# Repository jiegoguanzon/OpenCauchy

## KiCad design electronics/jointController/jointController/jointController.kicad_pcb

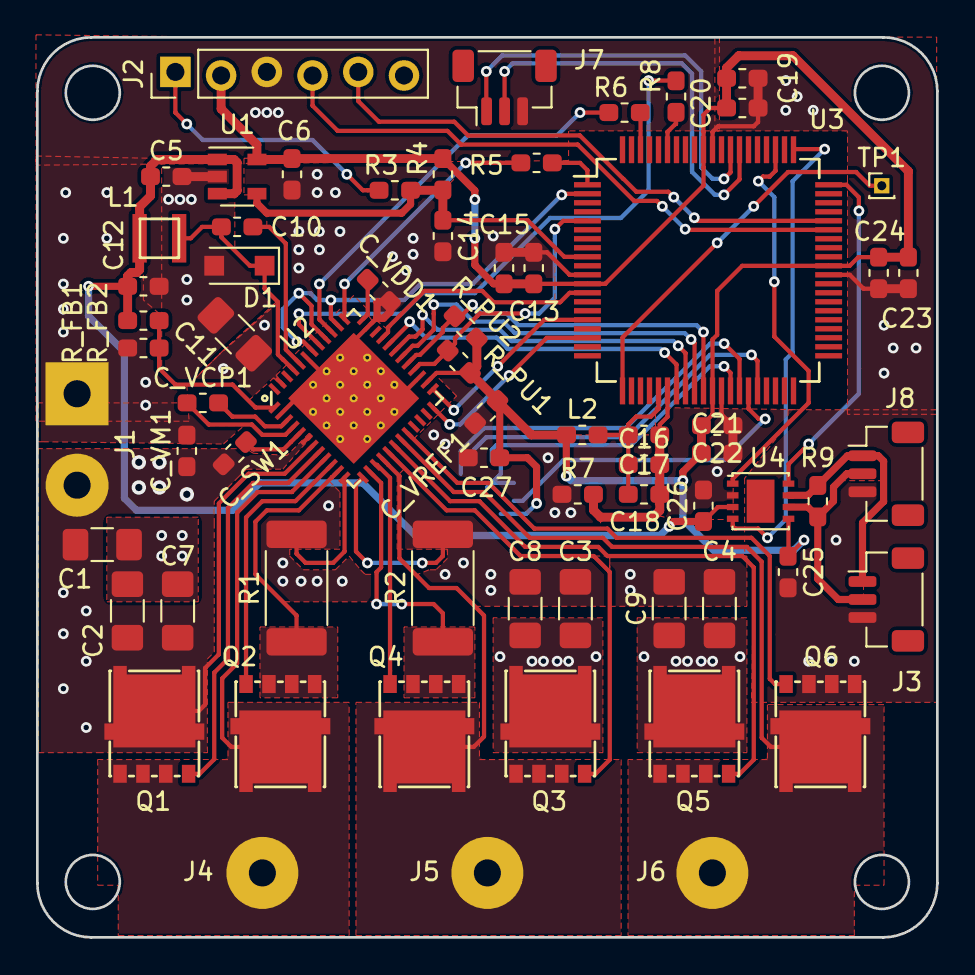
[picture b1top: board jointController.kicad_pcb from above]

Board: 2 copper layers, 50.0 x 50.0 mm, 68 parts (1 on the bottom side), 55 nets.

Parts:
C1, C2, C3, C4, C7, C8, C9, C11: 10uF; C_1206_3216Metric_Pad1.42x1.75mm_HandSolder
C5, C6, C16: 10uF; C_0603_1608Metric_Pad1.05x0.95mm_HandSolder
C10, C15, C17, C18, C20, C21, C23, C25, C26: 0.1uF; C_0603_1608Metric_Pad1.05x0.95mm_HandSolder
C12: 22uF; C_0603_1608Metric_Pad1.05x0.95mm_HandSolder
C13, C19, C22, C24: 0.01uF; C_0603_1608Metric_Pad1.05x0.95mm_HandSolder
C14: 470pF; C_0603_1608Metric_Pad1.05x0.95mm_HandSolder
C27: 1uF; C_0603_1608Metric_Pad1.05x0.95mm_HandSolder
C_SW1: 1uF; C_0603_1608Metric_Pad1.05x0.95mm_HandSolder
C_VCP1: 47nF; C_0603_1608Metric_Pad1.05x0.95mm_HandSolder
C_VDD1: 1uF; C_0603_1608Metric_Pad1.05x0.95mm_HandSolder
C_VM1: 0.1uF; C_0603_1608Metric_Pad1.05x0.95mm_HandSolder
C_VREF1: 0.1uF; C_0603_1608Metric_Pad1.05x0.95mm_HandSolder
D1: D_Schottky; D_SOD-123F
J1: PWR_IN; SolderWirePad_1x02_P5.08mm_Drill1.5mm
J2: ICSP; PinHeader_1x06_P2.54mm_Vertical_Staggered
J3, J8: CAN; JST_SH_BM03B-SRSS-TB_1x03-1MP_P1.00mm_Vertical
J4: A_OUT; SolderWirePad_1x01_Drill1.5mm
J5: B_OUT; SolderWirePad_1x01_Drill1.5mm
J6: C_OUT; SolderWirePad_1x01_Drill1.5mm
J7: UART1; JST_SH_BM03B-SRSS-TB_1x03-1MP_P1.00mm_Vertical
L1: 22uH; NRH3012T220MN
L2: 600R; L_0603_1608Metric_Pad1.05x0.95mm_HandSolder
Q1, Q2, Q3, Q4, Q5, Q6: NTMFS4935NT1G; 8-SOFL
R1, R2: 1m; R_2512_6332Metric_Pad1.52x3.35mm_HandSolder
R3, R7: 0; R_0603_1608Metric_Pad1.05x0.95mm_HandSolder
R4: 10k; R_0603_1608Metric_Pad1.05x0.95mm_HandSolder
R5, R6, R8: 75; R_0603_1608Metric_Pad1.05x0.95mm_HandSolder
R9: 120; R_0603_1608Metric_Pad1.05x0.95mm_HandSolder
R_FB1: 54.9k; R_0603_1608Metric_Pad1.05x0.95mm_HandSolder
R_FB2: 10k; R_0603_1608Metric_Pad1.05x0.95mm_HandSolder
R_PU1, R_PU2: 10k; R_0603_1608Metric_Pad1.05x0.95mm_HandSolder
TP1: DACOUT1; PinHeader_1x01_P1.00mm_Vertical
U1: MCP1755-3v3; SOT-23-5
U2: DRV8323RS; VQFN-48-7x7-P0.5
U3: dsPIC33CK256MP508; TQFP-80_12x12mm_P0.5mm
U4: MCP2562-E-MF; DFN-8-1EP_3x3mm_P0.65mm_EP1.55x2.4mm
U5: MA702; QFN-16-1EP_3x3mm_P0.5mm_EP1.8x1.8mm

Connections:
+3V3: C6.1, C13.2, C15.2, C19.2, C20.2, C21.2, C22.2, C23.1, C24.1, C25.1, C27.1, C_VREF1.1, J2.2, L2.1, R4.1, R_PU1.1, R_PU2.1, U1.5, U2.26, U3.12, U3.31, U3.51, U3.71, U4.5, U5.13
+5V: C5.1, C12.1, C26.1, L1.2, R_FB1.1, U1.1, U1.3, U4.3
A_OUT: J4.1, Q1.3, Q2.1, U2.9
B_OUT: J5.1, Q3.3, Q4.1, U2.16
CANH: J3.1, J8.1, R9.1, U4.7
CANL: J3.2, J8.2, R9.2, U4.6
CAN_RX: U3.61, U4.4
CAN_TX: U3.63, U4.1
C_OUT: J6.1, Q5.3, Q6.1, U2.19
DRV_ENABLE: U2.33, U3.13
DRV_MISO: R_PU2.2, U2.29, U3.30
DRV_MOSI: U2.30, U3.29
DRV_SCLK: U2.31, U3.28
DRV_nSCS: U2.32, U3.27
ENC_MISO: U3.33, U5.7
ENC_MOSI: U3.34, U5.4
ENC_SCLK: U3.35, U5.12
ENC_nSCS: U3.36, U5.5
GHA: Q1.2, U2.8
GHB: Q3.2, U2.17
GHC: Q5.2, U2.18
GLA: Q2.2, U2.10
GLB: Q4.2, U2.15
GLC: Q6.2, U2.20
GNDA: C16.2, C17.1, C18.2, R7.2, U3.26
unnamed: C10.1, U2.44
unnamed: C10.2, D1.1, L1.1, U2.45
unnamed: C16.1, C17.2, C18.1, L2.2, U3.25
unnamed: C_SW1.1, U2.5
unnamed: C_VCP1.1, U2.3
unnamed: C_VCP1.2, U2.4
unnamed: C_VDD1.2, U2.36
unnamed: R5.1, U3.1
unnamed: R6.1, U3.78
unnamed: R8.1, U3.75
unnamed: R_FB1.2, R_FB2.1, U2.1
unnamed: TP1.1, U3.21
PGC3: J2.5, U3.56
PGD3: J2.4, U3.55
PWM1H: R5.2, U2.37
PWM2H: R6.2, U2.39
PWM3H: R8.2, U2.41
PWM_EN: U2.38, U2.40, U2.42, U3.2
PWRGD: C14.1, R3.1, R4.2, U1.4, U3.9
SNA: C1.2, C2.2, C3.2, C4.2, C5.2, C6.2, C7.2, C8.2, C9.2, C11.2, C12.2, C13.1, C14.2, C15.1, C19.1, C20.1, C21.1, C22.1, C23.2, C24.2, C25.2, C26.2, C27.2, C_VDD1.1, C_VM1.2, C_VREF1.2, D1.2, J1.1, J2.3, J3.3, J7.3, J8.3, Q6.3, R1.2, R2.2, R7.1, R_FB2.2, U1.2, U2.2, U2.12, U2.13, U2.27, U2.35, U2.43, U2.49, U3.11, U3.32, U3.50, U3.70, U4.2, U5.8, U5.10, U5.17
SOA: U2.25, U3.16
SOB: U2.24, U3.18
SPA: Q2.3, R1.1, U2.11
SPB: Q4.3, R2.1, U2.14
STBY: U3.60, U4.8
UART_RX: J7.2, U3.67
UART_TX: J7.1, U3.68
V_DRAIN: C1.1, C2.1, C3.1, C4.1, C7.1, C8.1, C9.1, C11.1, C_SW1.2, C_VM1.1, J1.2, Q1.1, Q3.1, Q5.1, U2.6, U2.7, U2.47
nFAULT: R_PU1.2, U2.28, U3.5
nMCLR: J2.1, R3.2

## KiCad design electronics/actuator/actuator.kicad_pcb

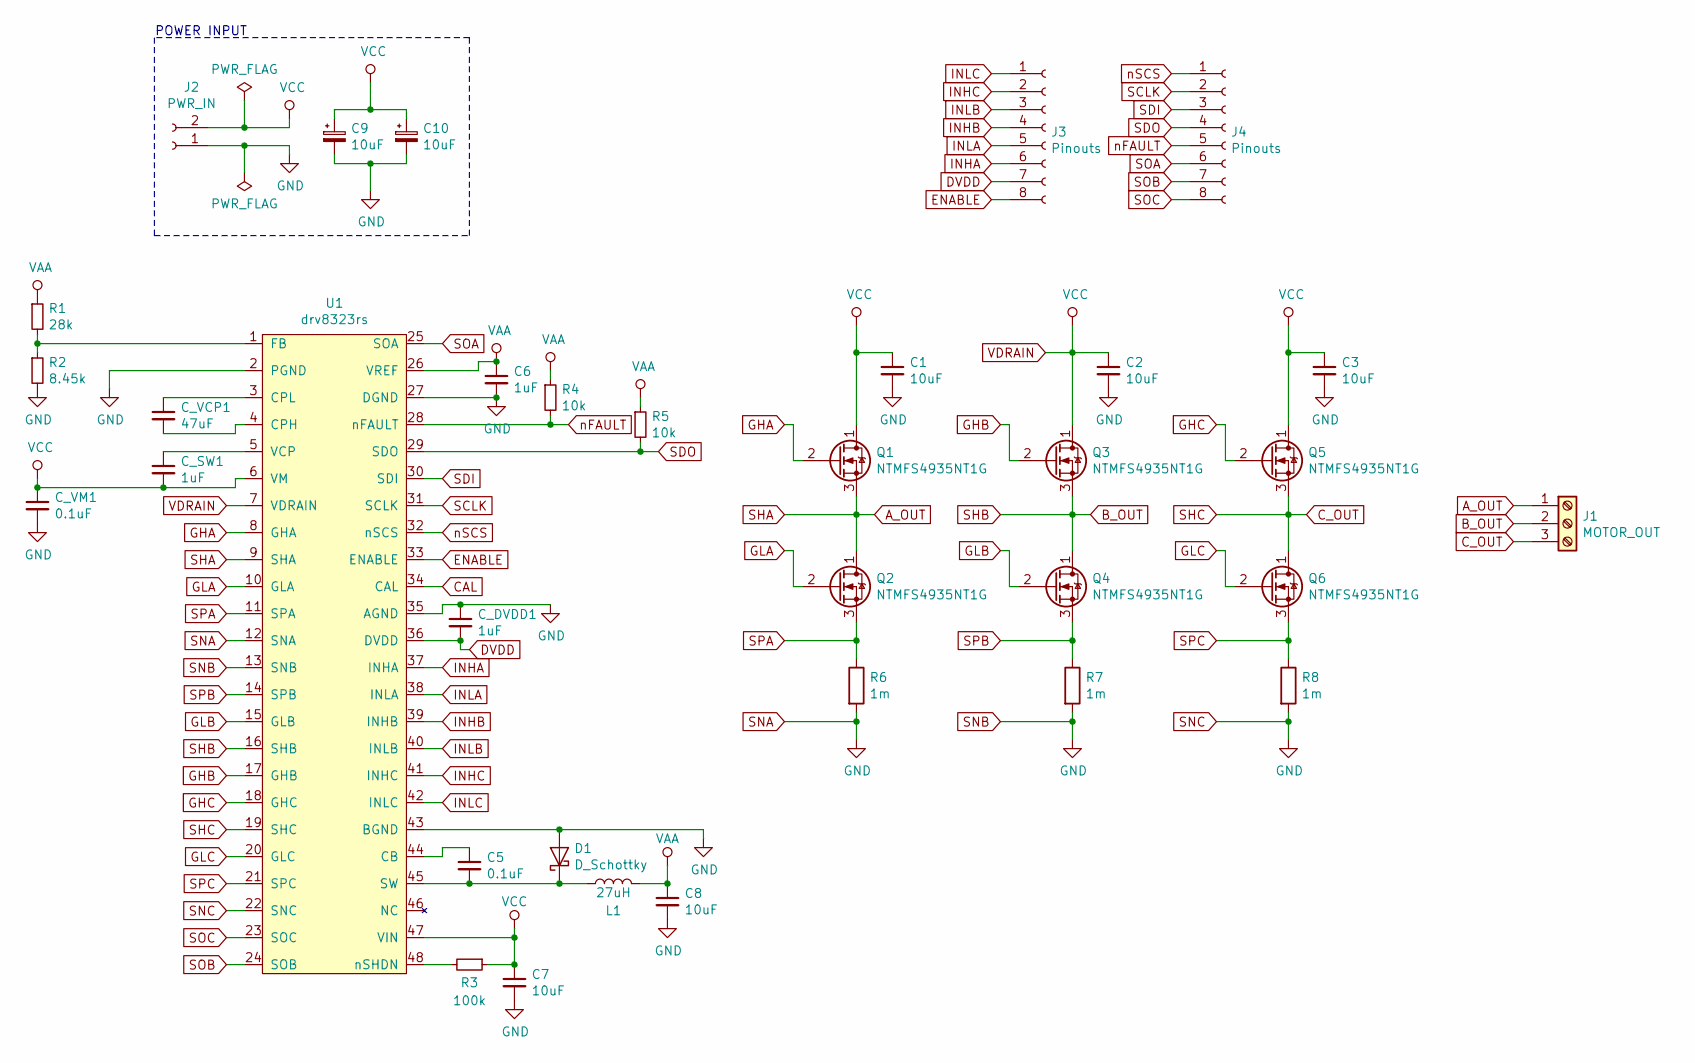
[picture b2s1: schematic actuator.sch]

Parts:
C1, C2, C3, C7, C8: 10uF; C_1206_3216Metric
C5: 0.1uF; C_0603_1608Metric
C6: 1uF; C_0603_1608Metric
C9, C10: 10uF; CP_Elec_6.3x5.4
C_DVDD1: 1uF; C_0603_1608Metric
C_SW1: 1uF; C_0603_1608Metric
C_VCP1: 47uF; C_0603_1608Metric
C_VM1: 0.1uF; C_0603_1608Metric
D1: D_Schottky; D_SOD-123F
J1: MOTOR_OUT; PhoenixContact_GMSTBA_2,5_3-G-7,62_1x03_P7.62mm_Horizontal
J2: PWR_IN; PhoenixContact_GMSTBA_2,5_2-G-7,62_1x02_P7.62mm_Horizontal
J3, J4: Pinouts; PinSocket_1x08_P2.54mm_Vertical
L1: 27uH; L_Radial_D7.8mm_P5.00mm_Fastron_07HCP
Q1, Q2, Q3, Q4, Q5, Q6: NTMFS4935NT1G; SO-FL-8
R1: 28k; R_0603_1608Metric_Pad1.05x0.95mm_HandSolder
R2: 8.45k; R_0402_1005Metric
R3: 100k; R_0603_1608Metric_Pad1.05x0.95mm_HandSolder
R4, R5: 10k; R_0603_1608Metric_Pad1.05x0.95mm_HandSolder
R6, R7, R8: 1m; R_2512_6332Metric
U1: drv8323rs; Texas_S-PVQFN-N48_EP5.15x5.15mm_ThermalVias

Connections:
A_OUT: J1.1, Q1.3 (S), Q2.1 (D), U1.9 (SHA)
B_OUT: J1.2, Q3.3 (S), Q4.1 (D), U1.16 (SHB)
CAL: U1.34 (CAL)
C_OUT: J1.3, Q5.3 (S), Q6.1 (D), U1.19 (SHC)
DVDD: C_DVDD1.2, J3.7, U1.36 (DVDD)
ENABLE: J3.8, U1.33 (ENABLE)
GHA: Q1.2 (G), U1.8 (GHA)
GHB: Q3.2 (G), U1.17 (GHB)
GHC: Q5.2 (G), U1.18 (GHC)
GLA: Q2.2 (G), U1.10 (GLA)
GLB: Q4.2 (G), U1.15 (GLB)
GLC: Q6.2 (G), U1.20 (GLC)
INHA: J3.6, U1.37 (INHA)
INHB: J3.4, U1.39 (INHB)
INHC: J3.2, U1.41 (INHC)
INLA: J3.5, U1.38 (INLA)
INLB: J3.3, U1.40 (INLB)
INLC: J3.1, U1.42 (INLC)
unnamed: C5.1, U1.44 (CB)
unnamed: C5.2, D1.1 (K), L1.2, U1.45 (SW)
unnamed: C_SW1.1, U1.5 (VCP)
unnamed: C_VCP1.1, U1.3 (CPL)
unnamed: C_VCP1.2, U1.4 (CPH)
unnamed: R1.2, R2.1, U1.1 (FB)
unnamed: R3.2, U1.48 (nSHDN)
SCLK: J4.2, U1.31 (SCLK)
SDI: J4.3, U1.30 (SDI)
SDO: J4.4, R5.2, U1.29 (SDO)
SNA: C1.2, C2.2, C3.2, C6.2, C7.2, C8.2, C9.2, C10.2, C_DVDD1.1, C_VM1.2, D1.2 (A), J2.1, R2.2, R6.2, R7.2, R8.2, U1.2 (PGND), U1.12 (SNA), U1.13 (SNB), U1.22 (SNC), U1.27 (DGND), U1.35 (AGND), U1.43 (BGND)
SOA: J4.6, U1.25 (SOA)
SOB: J4.7, U1.24 (SOB)
SOC: J4.8, U1.23 (SOC)
SPA: Q2.3 (S), R6.1, U1.11 (SPA)
SPB: Q4.3 (S), R7.1, U1.14 (SPB)
SPC: Q6.3 (S), R8.1, U1.21 (SPC)
VAA: C6.1, C8.1, L1.1, R1.1, R4.1, R5.1, U1.26 (VREF)
VDRAIN: C1.1, C2.1, C3.1, C7.1, C9.1, C10.1, C_SW1.2, C_VM1.1, J2.2, Q1.1 (D), Q3.1 (D), Q5.1 (D), R3.1, U1.6 (VM), U1.7 (VDRAIN), U1.47 (VIN)
nFAULT: J4.5, R4.2, U1.28 (nFAULT)
nSCS: J4.1, U1.32 (nSCS)

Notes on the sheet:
POWER INPUT

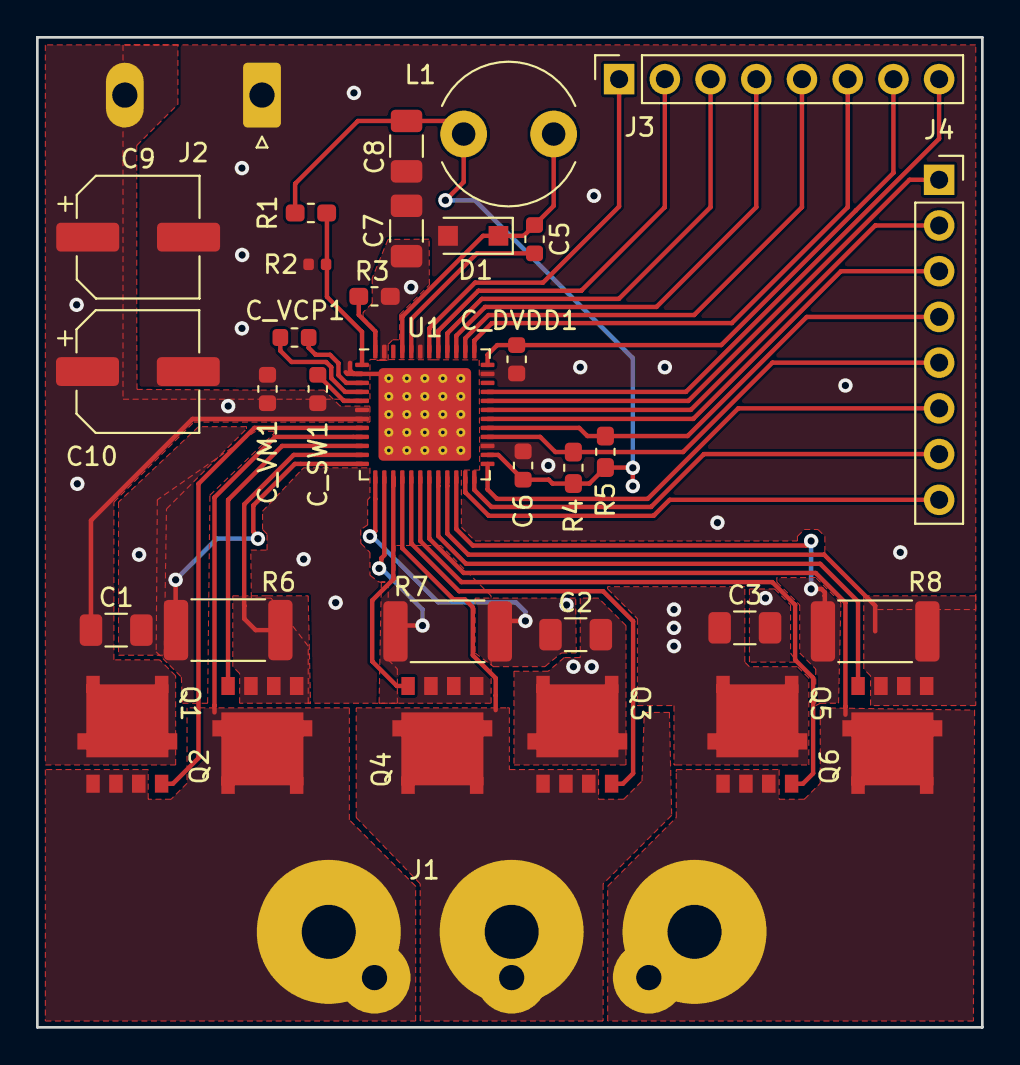
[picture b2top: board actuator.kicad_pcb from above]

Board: 2 copper layers, 52.5 x 55.0 mm, 34 parts (0 on the bottom side), 38 nets.

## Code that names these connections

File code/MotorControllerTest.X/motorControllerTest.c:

/*
 * File:   motorControllerTest.c
 * Author: jiego
 *
 * Created on September 12, 2019, 12:34 PM
 */

#define FCY 4000000

#include "xc.h"
#include "libpic30.h"

#pragma config FWDTEN = OFF
#pragma config JTAGEN = OFF
#pragma config POSCMOD = NONE
#pragma config OSCIOFNC = ON
#pragma config FCKSM = CSDCMD
#pragma config FNOSC = FRCPLL
#pragma config PLL96MHZ = OFF
#pragma config PLLDIV = NODIV
#pragma config SOSCSEL = IO

#define INHA    _LATB5
#define INLA    _LATB4
#define INHB    _LATB3
#define INLB    _LATB2
#define INHC    _LATB1
#define INLC    _LATB0

int main(void) {

    AD1PCFG = 0xFFFF;
    TRISB = 0xFF00;

    uint8_t state = 0;

    INHC = 1;
    INLC = 0;

    while (1) {

        /*
        switch (state) {
            case 0:
                INHA = 1;
                INLA = 0;
                INHB = 0;
                INLB = 1;
                INHC = 0;
                INLC = 0;
                break;
            case 1:
                INHA = 1;
                INLA = 0;
                INHB = 0;
                INLB = 0;
                INHC = 0;
                INLC = 1;
                break;
            case 2:
                INHA = 0;
                INLA = 0;
                INHB = 1;
                INLB = 0;
                INHC = 0;
                INLC = 1;
                break;
            case 3:
                INHA = 0;
                INLA = 1;
                INHB = 1;
                INLB = 0;
                INHC = 0;
                INLC = 0;
                break;
            case 4:
                INHA = 0;
                INLA = 1;
                INHB = 0;
                INLB = 0;
                INHC = 1;
                INLC = 0;
                break;
            case 5:
                INHA = 0;
                INLA = 0;
                INHB = 0;
                INLB = 1;
                INHC = 1;
                INLC = 0;
                break;
        }

        if (++state == 6)
            state = 0;
        */

        INHC = !_RB1;
        INLC = !_RB0;

        __delay_ms(100);

    }

    return 0;

}

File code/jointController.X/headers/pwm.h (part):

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       0 = If PCI current limit is active, then the CLDAT<1:0> bits define 
       the PWM output levels */
    PG1IOCONLbits.CLMOD = 0;
    /* Swap PWM Signals to PWM1H and PWM1L Device Pins bit 
       0 = PWM1H/L signals are mapped to their respective pins */
    PG1IOCONLbits.SWAP = 0;
    /* User Override Enable for PWM1H Pin bit
       0 = PWM Generator provides data for the PWM1H pin*/
    PG1IOCONLbits.OVRENH = 0;
    /* User Override Enable for PWM1L Pin bit
       0 = PWM Generator provides data for the PWM1L pin*/
    PG1IOCONLbits.OVRENL = 0;
    /* Data for PWM1H/PWM1L Pins if Override is Enabled bits
       If OVERENH = 1, then OVRDAT<1> provides data for PWM1H.
       If OVERENL = 1, then OVRDAT<0> provides data for PWM1L */
    PG1IOCONLbits.OVRDAT = 0;
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       00 = User output overrides via the OVRENL/H and OVRDAT<1:0> bits are 
       synchronized to the local PWM time base (next start of cycle)*/
    PG1IOCONLbits.OSYNC = 0;
    /* Data for PWM1H/PWM1L Pins if FLT Event is Active bits
       If Fault is active, then FLTDAT<1> provides data for PWM1H.
       If Fault is active, then FLTDAT<0> provides data for PWM1L.*/
    PG1IOCONLbits.FLTDAT = 0;
    /* Data for PWM1H/PWM1L Pins if CLMT Event is Active bits
       If current limit is active, then CLDAT<1> provides data for PWM1H.
       If current limit is active, then CLDAT<0> provides data for PWM1L.*/
    PG1IOCONLbits.CLDAT = 0;
    /* Data for PWM1H/PWM1L Pins if Feed-Forward Event is Active bits
       If feed-forward is active, then FFDAT<1> provides data for PWM1H.
       If feed-forward is active, then FFDAT<0> provides data for PWM1L.*/
    PG1IOCONLbits.FFDAT = 0;
    /* Data for PWM1H/PWM1L Pins if Debug Mode is Active and PTFRZ = 1 bits
       If Debug mode is active and PTFRZ=1,then DBDAT<1> provides PWM1H data.
       If Debug mode is active and PTFRZ=1,then DBDAT<0> provides PWM1L data. */
    PG1IOCONLbits.DBDAT = 0;
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       00 = PWM Generator outputs operate in Complementary mode*/
    PG1IOCONHbits.PMOD = 0;
    /* PWM1H Output Port Enable bit
       1 = PWM Generator controls the PWM1H output pin
       0 = PWM Generator does not control the PWM1H output pin */
    PG1IOCONHbits.PENH = 1;
    /* PWM1L Output Port Enable bit
       1 = PWM Generator controls the PWM1L output pin
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       0 = If PCI current limit is active, then the CLDAT<1:0> bits define 
       the PWM output levels */
    PG2IOCONLbits.CLMOD = 0;
    /* Swap PWM Signals to PWM2H and PWM2L Device Pins bit 
       0 = PWM2H/L signals are mapped to their respective pins */
    PG2IOCONLbits.SWAP = 0;
    /* User Override Enable for PWM2H Pin bit
       0 = PWM Generator provides data for the PWM2H pin*/
    PG2IOCONLbits.OVRENH = 0;
    /* User Override Enable for PWM2L Pin bit
       0 = PWM Generator provides data for the PWM2L pin*/
    PG2IOCONLbits.OVRENL = 0;
    /* Data for PWM2H/PWM2L Pins if Override is Enabled bits
       If OVERENH = 1, then OVRDAT<1> provides data for PWM2H.
       If OVERENL = 1, then OVRDAT<0> provides data for PWM2L */
    PG2IOCONLbits.OVRDAT = 0;
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       00 = User output overrides via the OVRENL/H and OVRDAT<1:0> bits are 
       synchronized to the local PWM time base (next start of cycle)*/
    PG2IOCONLbits.OSYNC = 0;
    /* Data for PWM2H/PWM2L Pins if FLT Event is Active bits
       If Fault is active, then FLTDAT<1> provides data for PWM2H.
       If Fault is active, then FLTDAT<0> provides data for PWM2L.*/
    PG2IOCONLbits.FLTDAT = 0;
    /* Data for PWM2H/PWM2L Pins if CLMT Event is Active bits
       If current limit is active, then CLDAT<1> provides data for PWM2H.
       If current limit is active, then CLDAT<0> provides data for PWM2L.*/
    PG2IOCONLbits.CLDAT = 0;
    /* Data for PWM2H/PWM2L Pins if Feed-Forward Event is Active bits
       If feed-forward is active, then FFDAT<1> provides data for PWM2H.
       If feed-forward is active, then FFDAT<0> provides data for PWM2L.*/
    PG2IOCONLbits.FFDAT = 0;
    /* Data for PWM2H/PWM2L Pins if Debug Mode is Active and PTFRZ = 1 bits
       If Debug mode is active and PTFRZ=1,then DBDAT<1> provides PWM2H data.
       If Debug mode is active and PTFRZ=1,then DBDAT<0> provides PWM2L data. */
    PG2IOCONLbits.DBDAT = 0;
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       00 = PWM Generator outputs operate in Complementary mode*/
    PG2IOCONHbits.PMOD = 0;
    /* PWM2H Output Port Enable bit
       1 = PWM Generator controls the PWM2H output pin
       0 = PWM Generator does not control the PWM2H output pin */
    PG2IOCONHbits.PENH = 1;
    /* PWM2L Output Port Enable bit
       1 = PWM Generator controls the PWM2L output pin
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       0 = If PCI current limit is active, then the CLDAT<1:0> bits define 
       the PWM output levels */
    PG3IOCONLbits.CLMOD = 0;
    /* Swap PWM Signals to PWM3H and PWM3L Device Pins bit 
       0 = PWM3H/L signals are mapped to their respective pins */
    PG3IOCONLbits.SWAP = 0;
    /* User Override Enable for PWM3H Pin bit
       0 = PWM Generator provides data for the PWM3H pin*/
    PG3IOCONLbits.OVRENH = 0;
    /* User Override Enable for PWM3L Pin bit
       0 = PWM Generator provides data for the PWM3L pin*/
    PG3IOCONLbits.OVRENL = 0;
    /* Data for PWM3H/PWM3L Pins if Override is Enabled bits
       If OVERENH = 1, then OVRDAT<1> provides data for PWM3H.
       If OVERENL = 1, then OVRDAT<0> provides data for PWM3L */
    PG3IOCONLbits.OVRDAT = 0;
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       00 = User output overrides via the OVRENL/H and OVRDAT<1:0> bits are 
       synchronized to the local PWM time base (next start of cycle)*/
    PG3IOCONLbits.OSYNC = 0;
    /* Data for PWM3H/PWM3L Pins if FLT Event is Active bits
       If Fault is active, then FLTDAT<1> provides data for PWM3H.
       If Fault is active, then FLTDAT<0> provides data for PWM3L.*/
    PG3IOCONLbits.FLTDAT = 0;
    /* Data for PWM3H/PWM3L Pins if CLMT Event is Active bits
       If current limit is active, then CLDAT<1> provides data for PWM3H.
       If current limit is active, then CLDAT<0> provides data for PWM3L.*/
    PG3IOCONLbits.CLDAT = 0;
    /* Data for PWM3H/PWM3L Pins if Feed-Forward Event is Active bits
       If feed-forward is active, then FFDAT<1> provides data for PWM3H.
       If feed-forward is active, then FFDAT<0> provides data for PWM3L.*/
    PG3IOCONLbits.FFDAT = 0;
    /* Data for PWM3H/PWM3L Pins if Debug Mode is Active and PTFRZ = 1 bits
       If Debug mode is active and PTFRZ=1,then DBDAT<1> provides PWM3H data.
       If Debug mode is active and PTFRZ=1,then DBDAT<0> provides PWM3L data. */
    PG3IOCONLbits.DBDAT = 0;
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       00 = PWM Generator outputs operate in Complementary mode*/
    PG3IOCONHbits.PMOD = 0;
    /* PWM3H Output Port Enable bit
       1 = PWM Generator controls the PWM3H output pin
       0 = PWM Generator does not control the PWM3H output pin */
    PG3IOCONHbits.PENH = 1;
    /* PWM3L Output Port Enable bit
       1 = PWM Generator controls the PWM3L output pin
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
void pwm_disable_outputs () {

    PG3IOCONLbits.OVRDAT = 0;  // 0b00 = State for PWM3H,L, if Override is Enabled
    PG2IOCONLbits.OVRDAT = 0;  // 0b00 = State for PWM2H,L, if Override is Enabled
    PG1IOCONLbits.OVRDAT = 0;  // 0b00 = State for PWM1H,L, if Override is Enabled

    PG3IOCONLbits.OVRENH = 1;  // 0 = PWM generator provides data for PWM3H pin
    PG2IOCONLbits.OVRENH = 1;  // 0 = PWM generator provides data for PWM2H pin
    PG1IOCONLbits.OVRENH = 1;  // 0 = PWM generator provides data for PWM1H pin

    PG3IOCONLbits.OVRENL = 1;  // 0 = PWM generator provides data for PWM3L pin
    PG2IOCONLbits.OVRENL = 1;  // 0 = PWM generator provides data for PWM2L pin
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
void pwm_enable_outputs () {

    PG3IOCONLbits.OVRDAT = 0;  // 0b00 = State for PWM3H,L, if Override is Enabled
    PG2IOCONLbits.OVRDAT = 0;  // 0b00 = State for PWM2H,L, if Override is Enabled
    PG1IOCONLbits.OVRDAT = 0;  // 0b00 = State for PWM1H,L, if Override is Enabled

    PG3IOCONLbits.OVRENH = 0;  // 0 = PWM generator provides data for PWM3H pin
    PG2IOCONLbits.OVRENH = 0;  // 0 = PWM generator provides data for PWM2H pin
    PG1IOCONLbits.OVRENH = 0;  // 0 = PWM generator provides data for PWM1H pin

    PG3IOCONLbits.OVRENL = 0;  // 0 = PWM generator provides data for PWM3L pin
    PG2IOCONLbits.OVRENL = 0;  // 0 = PWM generator provides data for PWM2L pin
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
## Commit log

2019-08-01 Initial commit.
2019-08-20 Added motor controller schematic.
2019-08-21 Added new motor actuator.
2019-08-21 Added footprints.
2019-08-23 Added SO-FL-8 footprint.
2019-08-27 Added a bunch of stuff and initial layout.
2019-08-28 Started routing.
2019-08-28 Still routing...
2019-08-30 Still routing.
2019-08-30 Finished pcb.
2019-09-01 Finished board.
2019-09-02 Board ready for fab.
2019-09-24 Added code.
2019-09-24 Organized files.
2019-09-25 Updated board.
2019-09-25 Started motorController.X
2019-09-25 Started with SPI code.
2019-09-26 Finished SPI.
2019-09-27 FOC-ish.
2019-10-05 Fixing commits.
2019-10-07 Added v2.
2019-10-08 Started v2.
2019-10-08 Finished backplate.
2019-10-20 Yikes
2019-10-24 Added SVM.
2019-10-24 Finished SVM.
2019-11-05 Added dsPICDEM2.
2020-01-19 First commit of the year.
2020-01-20 Merging
2020-01-20 Fixed 90Mips FCY
2020-02-07 FOC done wahoo.
2020-02-22 FOC completed.
2020-02-23 Started jointController board.
2020-02-26 Almost done with jointControllerV1
2020-02-26 jointController V1.0 finished.
2020-03-08 Started CAN
